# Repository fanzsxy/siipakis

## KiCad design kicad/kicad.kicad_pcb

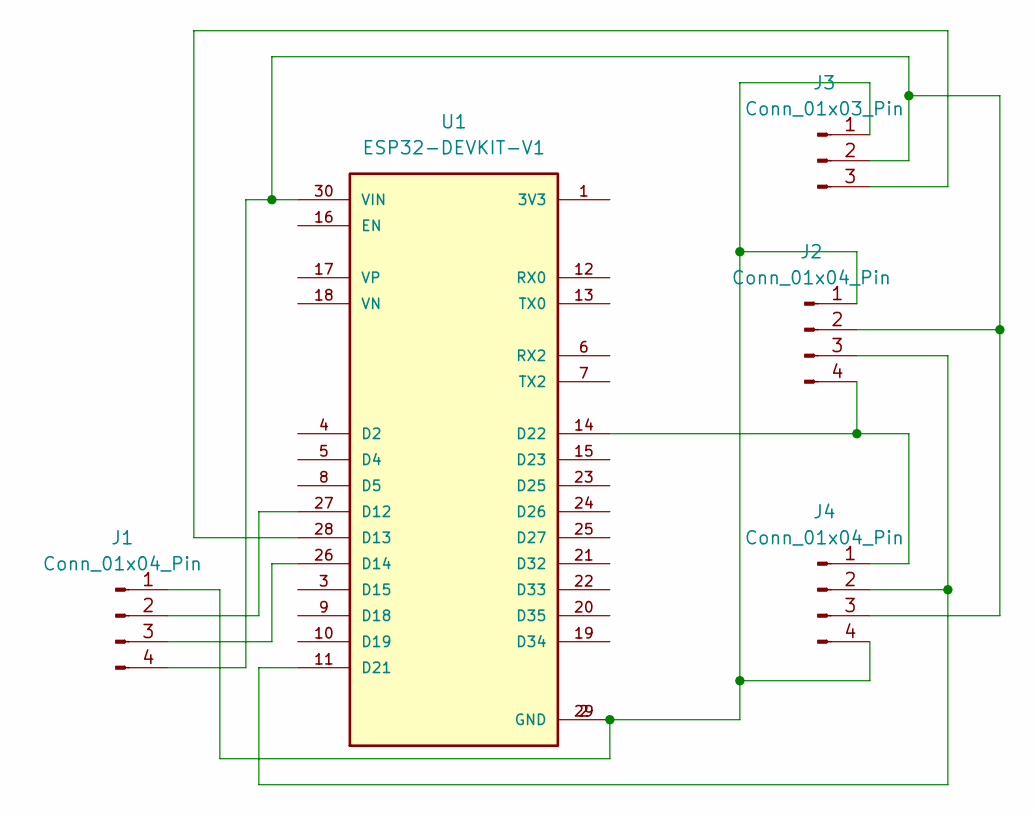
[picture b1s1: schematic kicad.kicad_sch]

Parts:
J1, J2, J4: Conn_01x04_Pin; FanPinHeader_1x04_P2.54mm_Vertical
J3: Conn_01x03_Pin; FanPinHeader_1x03_P2.54mm_Vertical
U1: ESP32-DEVKIT-V1; MODULE_ESP32_DEVKIT_V1; PARTREV N/A

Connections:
unnamed: J1.1, J2.1, J3.1, J4.4, U1.2 (GND), U1.29 (GND)
unnamed: J1.2, U1.27 (D12)
unnamed: J1.3, U1.26 (D14)
unnamed: J1.4, J2.2, J3.2, J4.3, U1.30 (VIN)
unnamed: J2.3, J4.2, U1.11 (D21)
unnamed: J2.4, J4.1, U1.14 (D22)
unnamed: J3.3, U1.28 (D13)

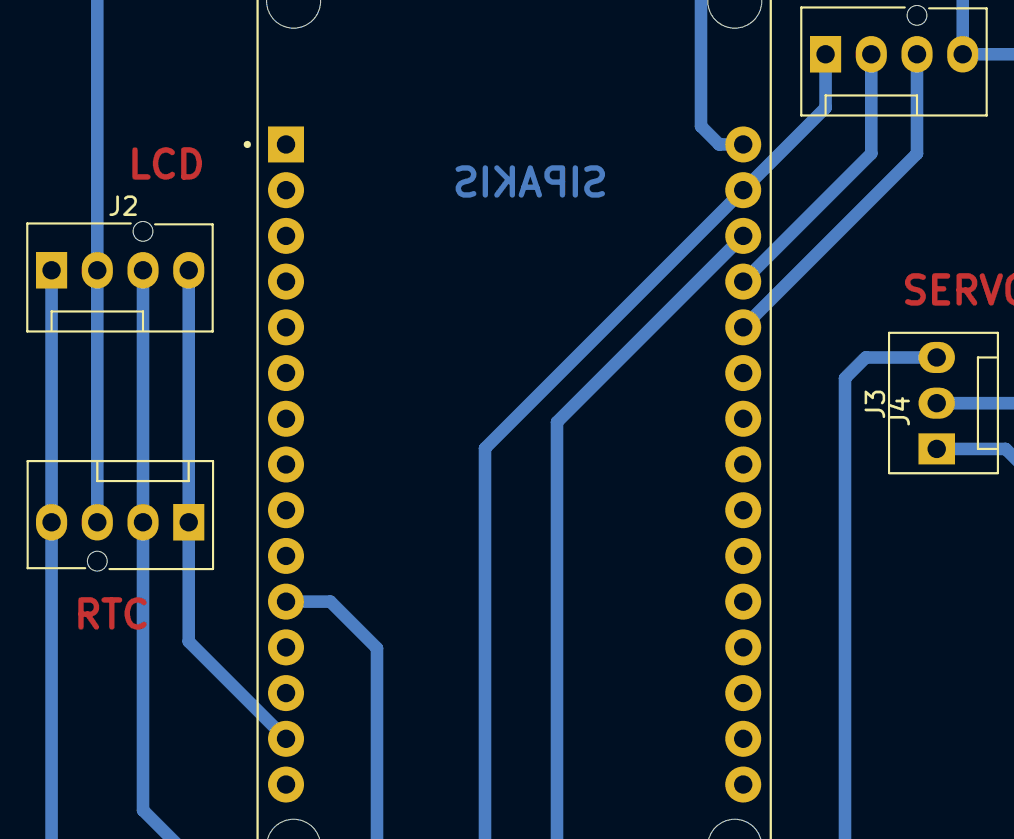
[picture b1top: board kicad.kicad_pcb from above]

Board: 2 copper layers, 5 parts (0 on the bottom side), 7 nets.

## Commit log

2025-06-14 sipakis
2025-06-14 sipakis2
2025-06-15 sipakis3
2025-06-15 sipakis3.1
2025-06-15 sipakis4
2025-06-16 sipakis4.1
2025-06-17 sipakis4.2
